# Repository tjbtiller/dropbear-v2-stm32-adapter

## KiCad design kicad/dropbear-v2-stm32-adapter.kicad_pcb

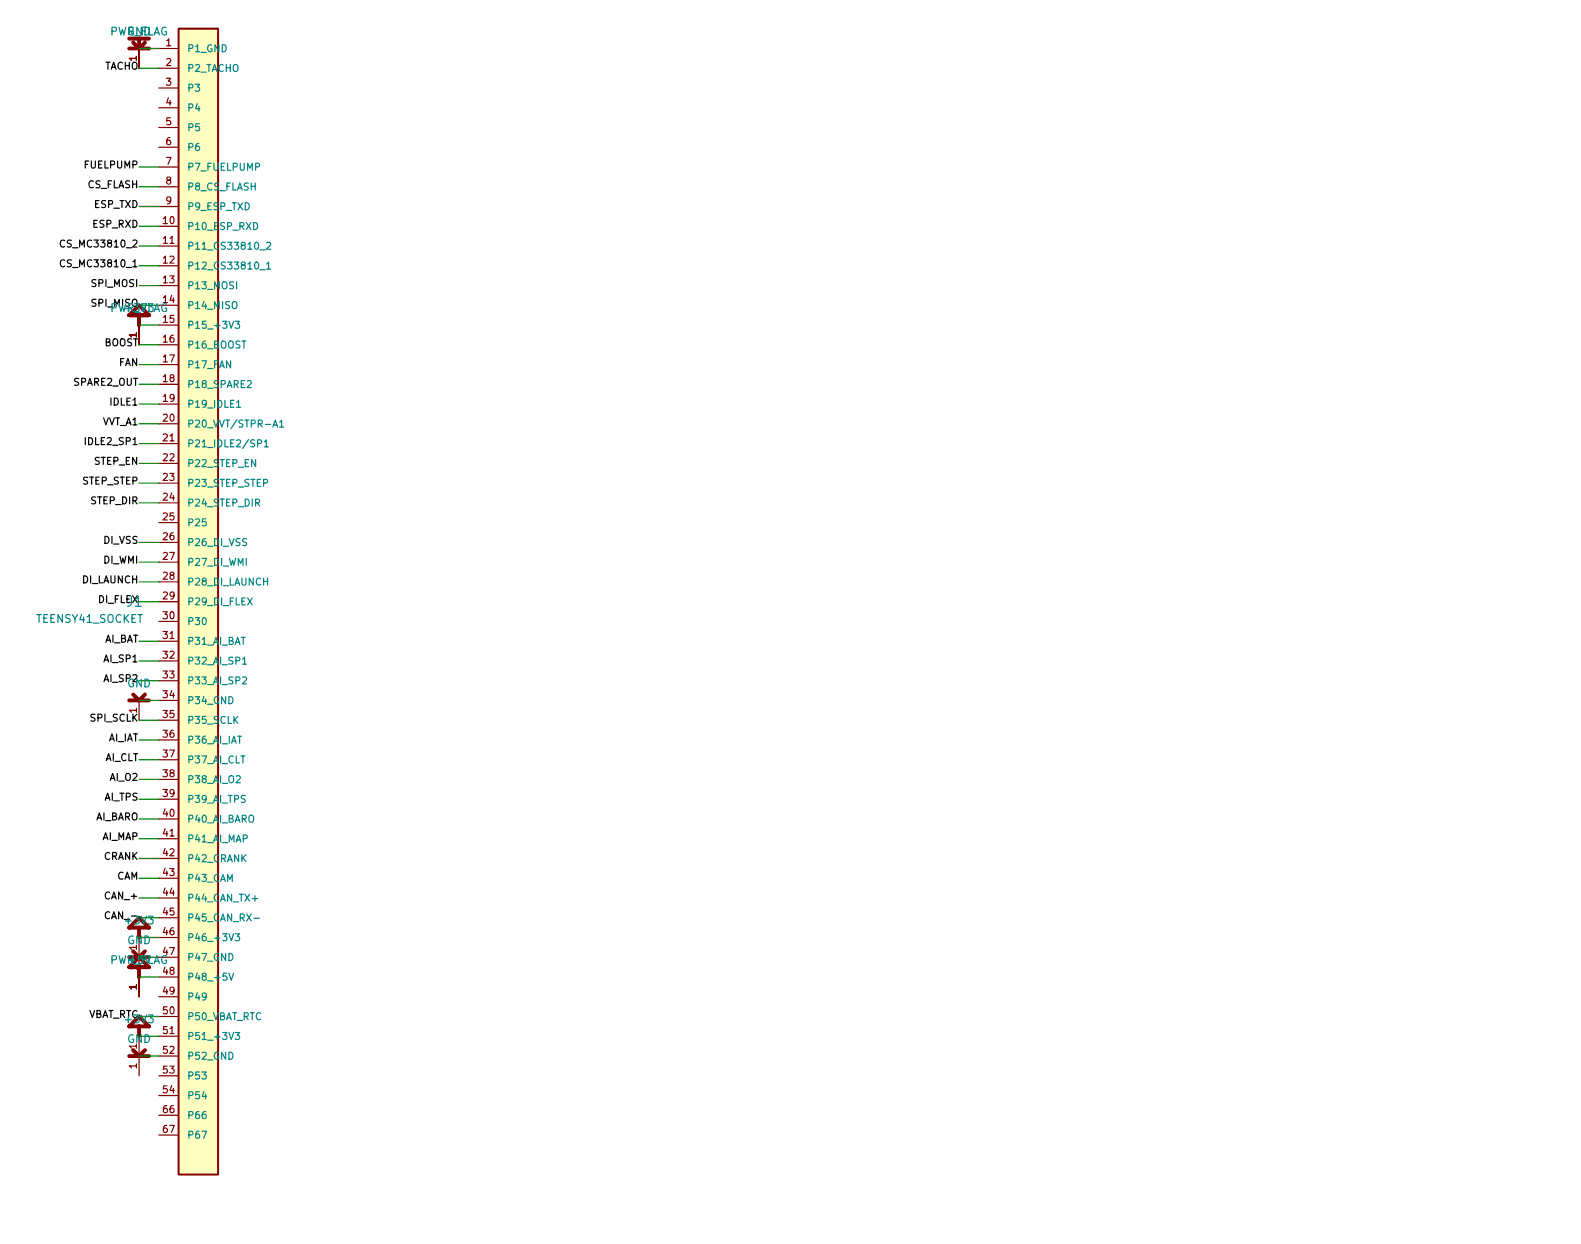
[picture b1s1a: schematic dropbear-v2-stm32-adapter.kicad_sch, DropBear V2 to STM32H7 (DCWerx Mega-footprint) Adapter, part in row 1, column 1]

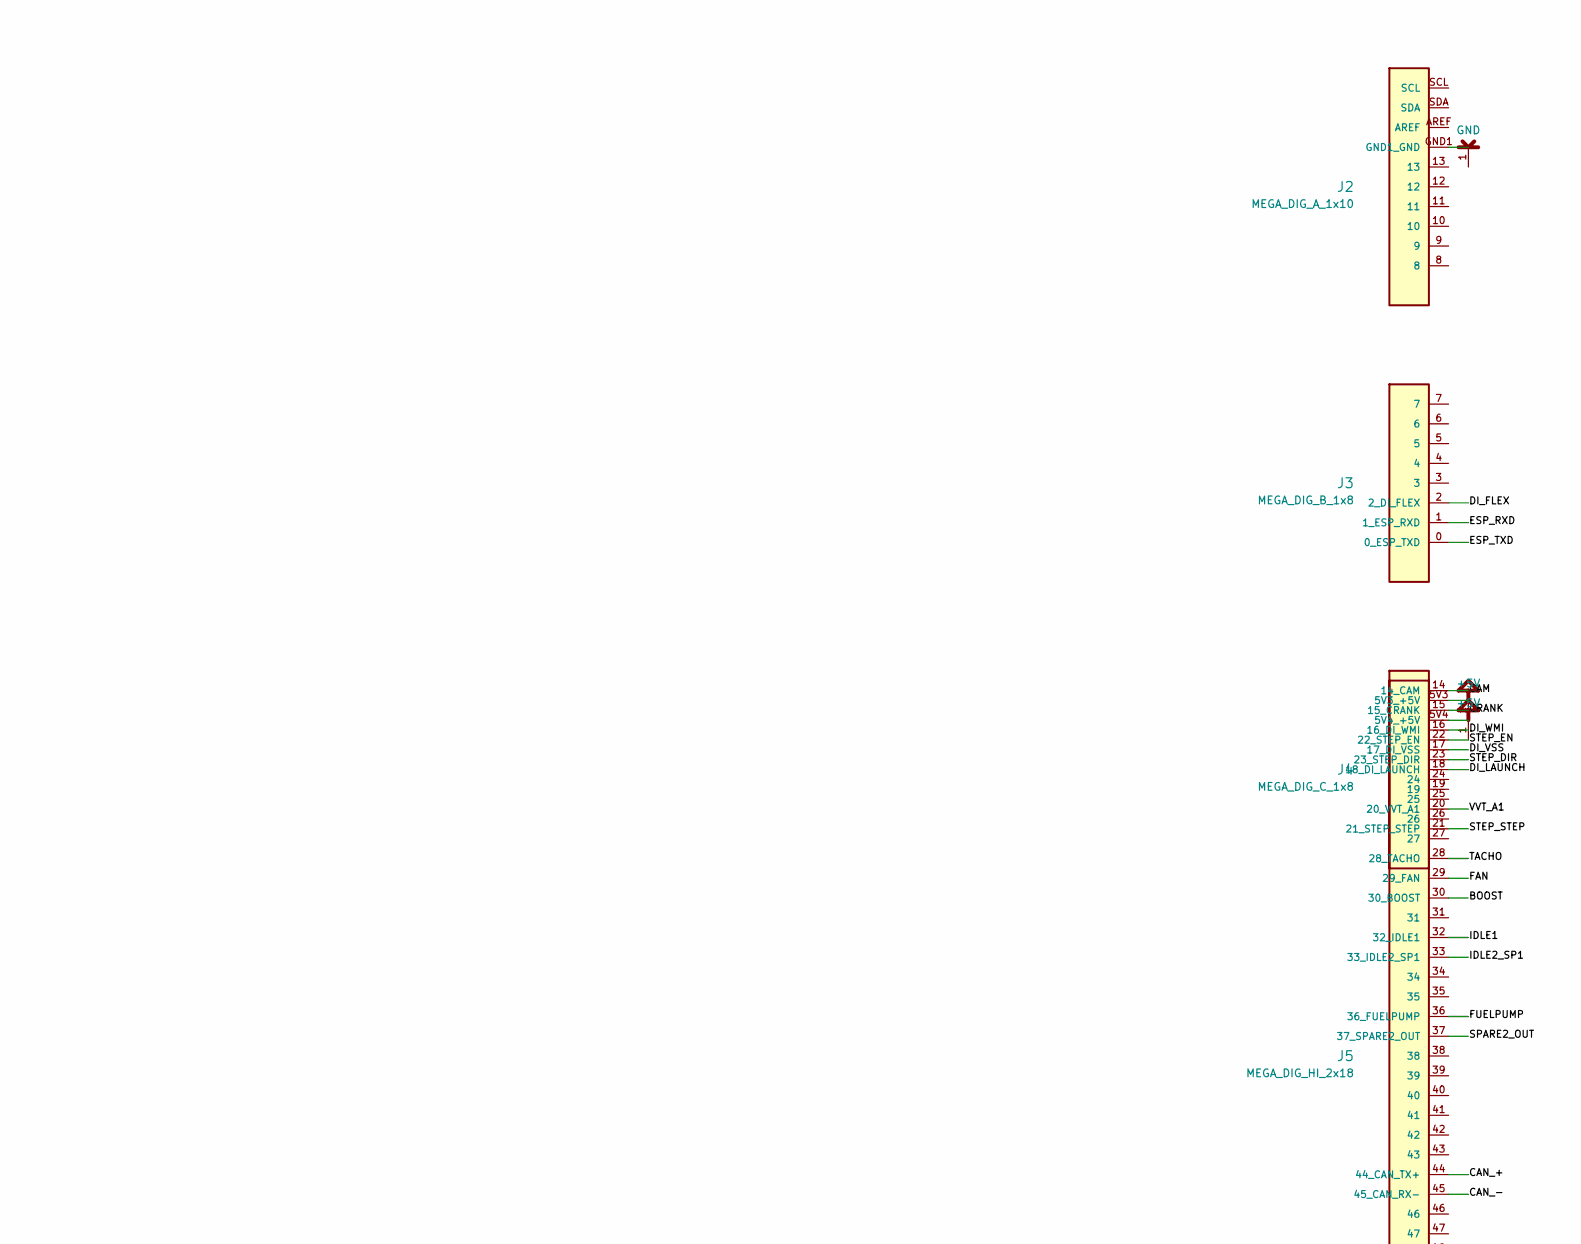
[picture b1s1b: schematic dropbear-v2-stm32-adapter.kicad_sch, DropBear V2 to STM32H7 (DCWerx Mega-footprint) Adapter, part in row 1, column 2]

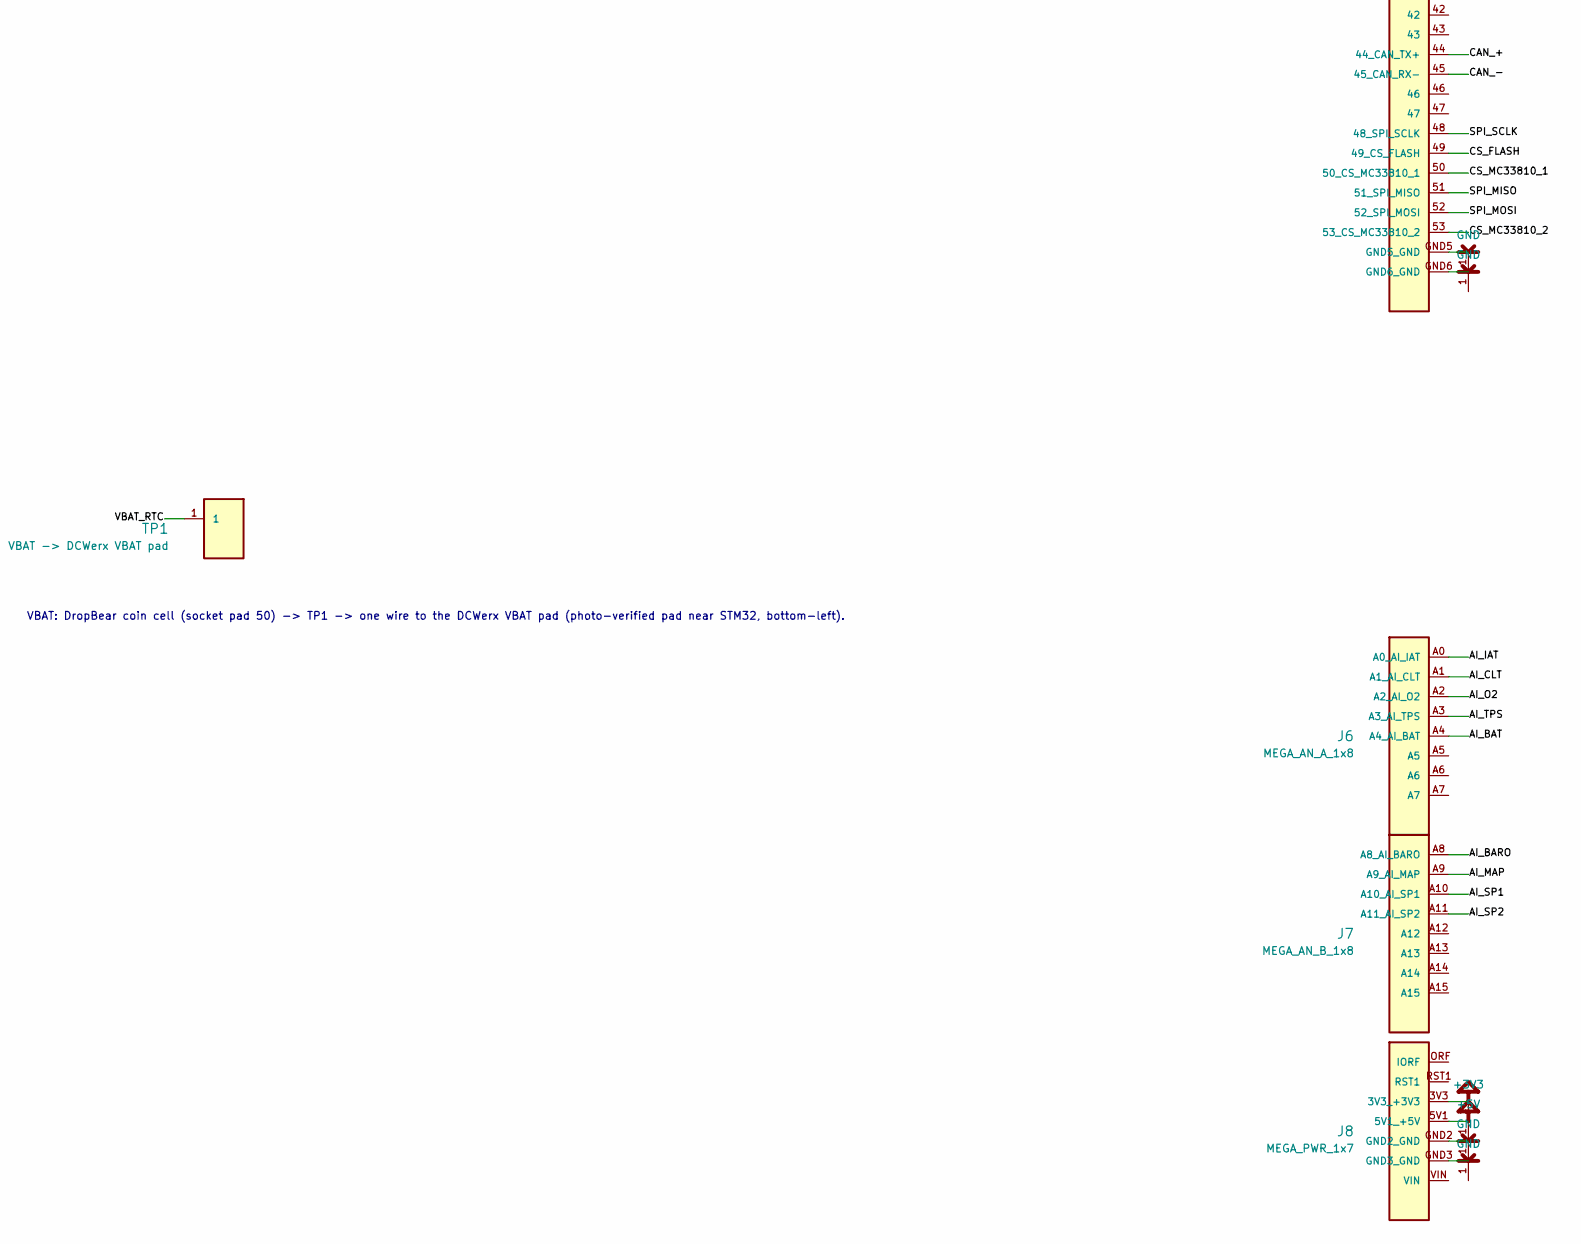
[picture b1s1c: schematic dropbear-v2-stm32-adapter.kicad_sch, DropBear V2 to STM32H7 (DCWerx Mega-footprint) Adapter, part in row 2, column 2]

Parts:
J1: TEENSY41_SOCKET
J2: MEGA_DIG_A_1x10
J3: MEGA_DIG_B_1x8
J4: MEGA_DIG_C_1x8
J5: MEGA_DIG_HI_2x18
J6: MEGA_AN_A_1x8
J7: MEGA_AN_B_1x8
J8: MEGA_PWR_1x7
TP1: VBAT -> DCWerx VBAT pad; TestPoint_THT_D2

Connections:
/AI_BARO: J1.40 (P40_AI_BARO), J7.A8 (A8_AI_BARO)
/AI_BAT: J1.31 (P31_AI_BAT), J6.A4 (A4_AI_BAT)
/AI_CLT: J1.37 (P37_AI_CLT), J6.A1 (A1_AI_CLT)
/AI_IAT: J1.36 (P36_AI_IAT), J6.A0 (A0_AI_IAT)
/AI_MAP: J1.41 (P41_AI_MAP), J7.A9 (A9_AI_MAP)
/AI_O2: J1.38 (P38_AI_O2), J6.A2 (A2_AI_O2)
/AI_SP1: J1.32 (P32_AI_SP1), J7.A10 (A10_AI_SP1)
/AI_SP2: J1.33 (P33_AI_SP2), J7.A11 (A11_AI_SP2)
/AI_TPS: J1.39 (P39_AI_TPS), J6.A3 (A3_AI_TPS)
/BOOST: J1.16 (P16_BOOST), J5.30 (30_BOOST)
/CAM: J1.43 (P43_CAM), J4.14 (14_CAM)
/CAN_+: J1.44 (P44_CAN_TX+), J5.44 (44_CAN_TX+)
/CAN_-: J1.45 (P45_CAN_RX-), J5.45 (45_CAN_RX-)
/CRANK: J1.42 (P42_CRANK), J4.15 (15_CRANK)
/CS_FLASH: J1.8 (P8_CS_FLASH), J5.49 (49_CS_FLASH)
/CS_MC33810_1: J1.12 (P12_CS33810_1), J5.50 (50_CS_MC33810_1)
/CS_MC33810_2: J1.11 (P11_CS33810_2), J5.53 (53_CS_MC33810_2)
/DI_FLEX: J1.29 (P29_DI_FLEX), J3.2 (2_DI_FLEX)
/DI_LAUNCH: J1.28 (P28_DI_LAUNCH), J4.18 (18_DI_LAUNCH)
/DI_VSS: J1.26 (P26_DI_VSS), J4.17 (17_DI_VSS)
/DI_WMI: J1.27 (P27_DI_WMI), J4.16 (16_DI_WMI)
/ESP_RXD: J1.10 (P10_ESP_RXD), J3.1 (1_ESP_RXD)
/ESP_TXD: J1.9 (P9_ESP_TXD), J3.0 (0_ESP_TXD)
/FAN: J1.17 (P17_FAN), J5.29 (29_FAN)
/FUELPUMP: J1.7 (P7_FUELPUMP), J5.36 (36_FUELPUMP)
/IDLE1: J1.19 (P19_IDLE1), J5.32 (32_IDLE1)
/IDLE2_SP1: J1.21 (P21_IDLE2/SP1), J5.33 (33_IDLE2_SP1)
/SPARE2_OUT: J1.18 (P18_SPARE2), J5.37 (37_SPARE2_OUT)
/SPI_MISO: J1.14 (P14_MISO), J5.51 (51_SPI_MISO)
/SPI_MOSI: J1.13 (P13_MOSI), J5.52 (52_SPI_MOSI)
/SPI_SCLK: J1.35 (P35_SCLK), J5.48 (48_SPI_SCLK)
/STEP_DIR: J1.24 (P24_STEP_DIR), J5.23 (23_STEP_DIR)
/STEP_EN: J1.22 (P22_STEP_EN), J5.22 (22_STEP_EN)
/STEP_STEP: J1.23 (P23_STEP_STEP), J4.21 (21_STEP_STEP)
/TACHO: J1.2 (P2_TACHO), J5.28 (28_TACHO)
/VBAT_RTC: J1.50 (P50_VBAT_RTC), TP1.1 (1_1)
/VVT_A1: J1.20 (P20_VVT/STPR-A1), J4.20 (20_VVT_A1)

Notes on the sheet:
VBAT: DropBear coin cell (socket pad 50) -> TP1 -> one wire to the DCWerx VBAT pad (photo-verified pad near STM32, bottom-left).

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
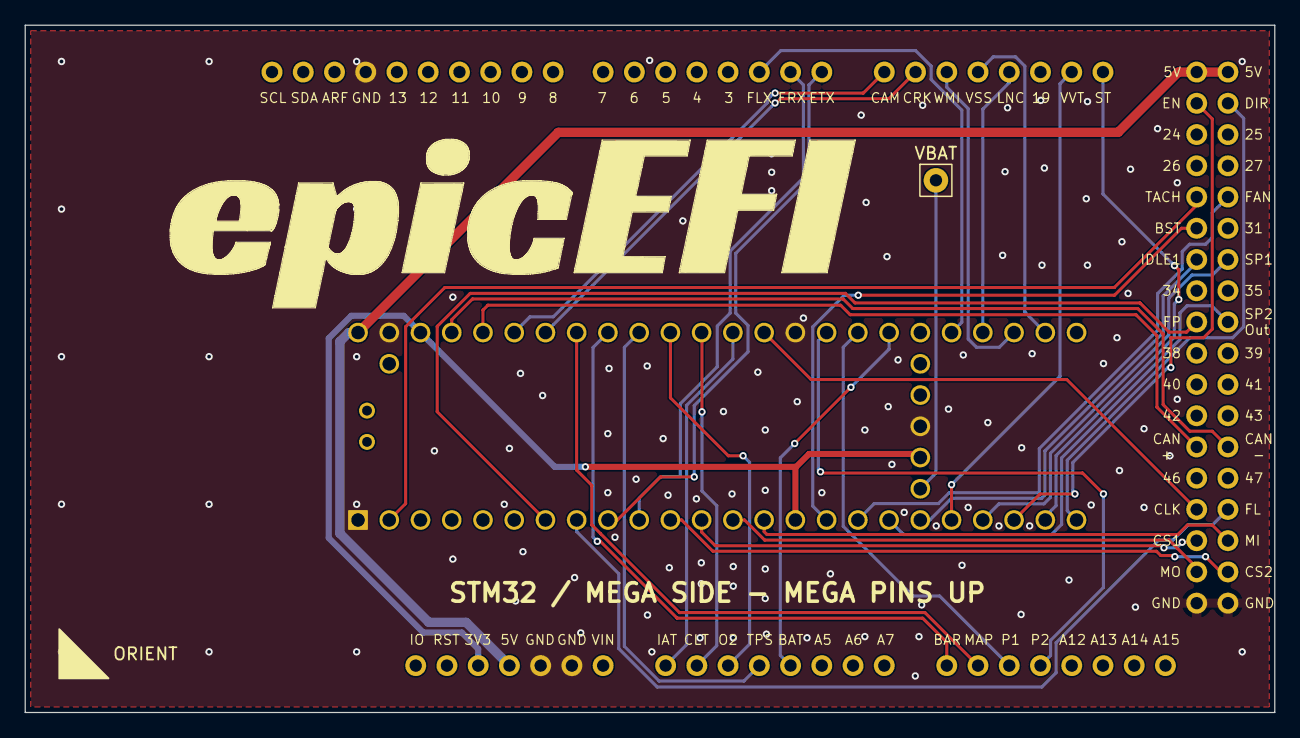
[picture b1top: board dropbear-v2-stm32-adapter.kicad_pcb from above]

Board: 2 copper layers, 101.6 x 55.9 mm, 9 parts (0 on the bottom side), 40 nets.

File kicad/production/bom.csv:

Designator,Footprint,Quantity,Value,LCSC Part #
J1,TEENSY41_SOCKET,1,TEENSY41_SOCKET,
J2,MEGA_DIG_A_1x10,1,MEGA_DIG_A_1x10,
J3,MEGA_DIG_B_1x8,1,MEGA_DIG_B_1x8,
J4,MEGA_DIG_C_1x8,1,MEGA_DIG_C_1x8,
J5,MEGA_DIG_HI_2x18,1,MEGA_DIG_HI_2x18,
J6,MEGA_AN_A_1x8,1,MEGA_AN_A_1x8,
J7,MEGA_AN_B_1x8,1,MEGA_AN_B_1x8,
J8,MEGA_PWR_1x7,1,MEGA_PWR_1x7,
TP1,TestPoint_THT_D2,1,VBAT -> DCWerx VBAT pad,
